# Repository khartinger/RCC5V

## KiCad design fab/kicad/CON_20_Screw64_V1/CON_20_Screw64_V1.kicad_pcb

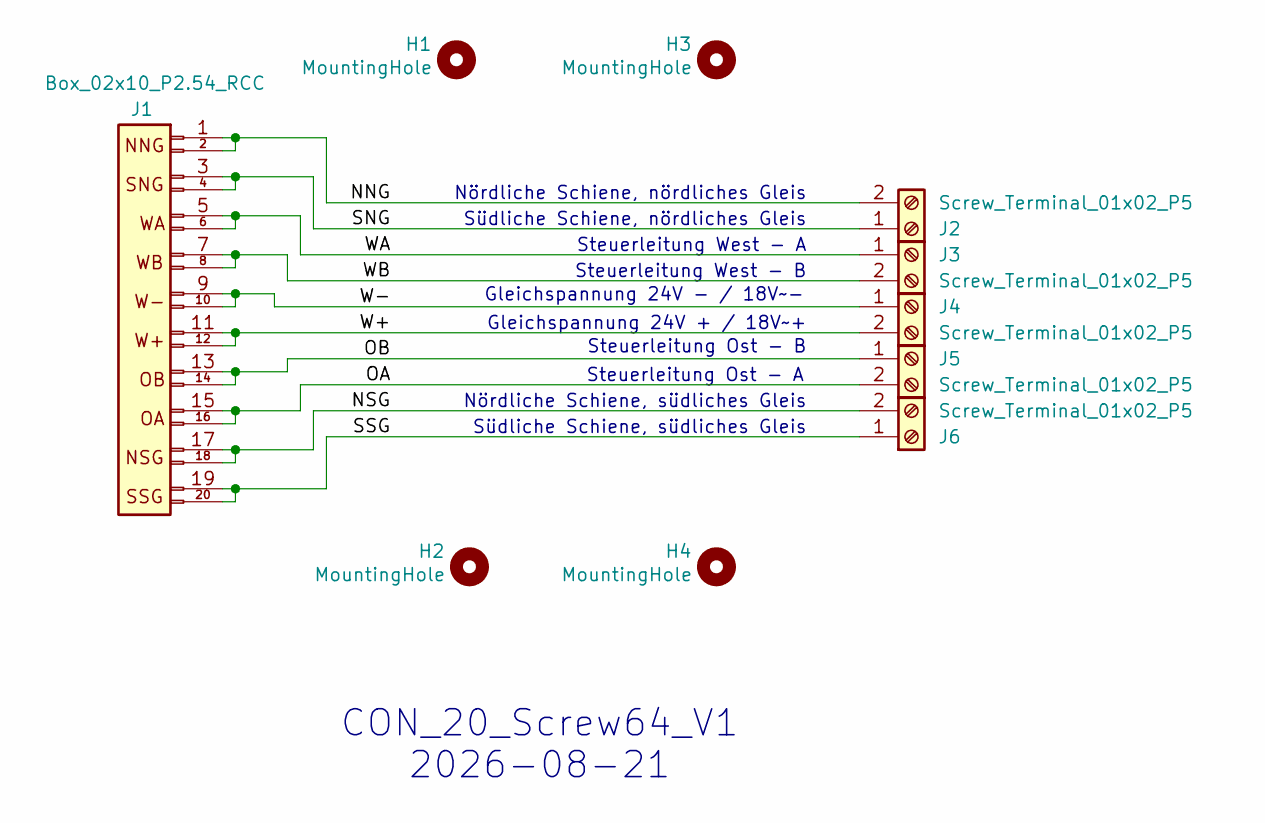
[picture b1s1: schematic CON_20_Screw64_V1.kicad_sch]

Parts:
H1, H2, H3, H4: MountingHole; MountingHole_2.7mm_M2.5_DIN965_Pad_TopBottom
J1: Box_02x10_P2.54_RCC; Box_02x10_P2.54mm_Vertical_kh
J2, J3, J4, J5, J6: Screw_Terminal_01x02_P5

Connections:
/NNG: J1.1, J1.2, J2.2
/NSG: J1.17, J1.18, J6.2
/OA: J1.15, J1.16, J5.2
/OB: J1.13, J1.14, J5.1
/SNG: J1.3, J1.4, J2.1
/SSG: J1.19, J1.20, J6.1
/W+: J1.11, J1.12, J4.2
/W-: J1.9, J1.10, J4.1
/WA: J1.5, J1.6, J3.1
/WB: J1.7, J1.8, J3.2

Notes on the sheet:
CON_20_Screw64_V1 2026-08-21
Südliche Schiene, südliches Gleis
Südliche Schiene, nördliches Gleis
Gleichspannung 24V - / 18V~-
Nördliche Schiene, nördliches Gleis
Steuerleitung West - A
Steuerleitung Ost - B
Steuerleitung West - B
Gleichspannung 24V + / 18V~+
Nördliche Schiene, südliches Gleis
Steuerleitung Ost - A

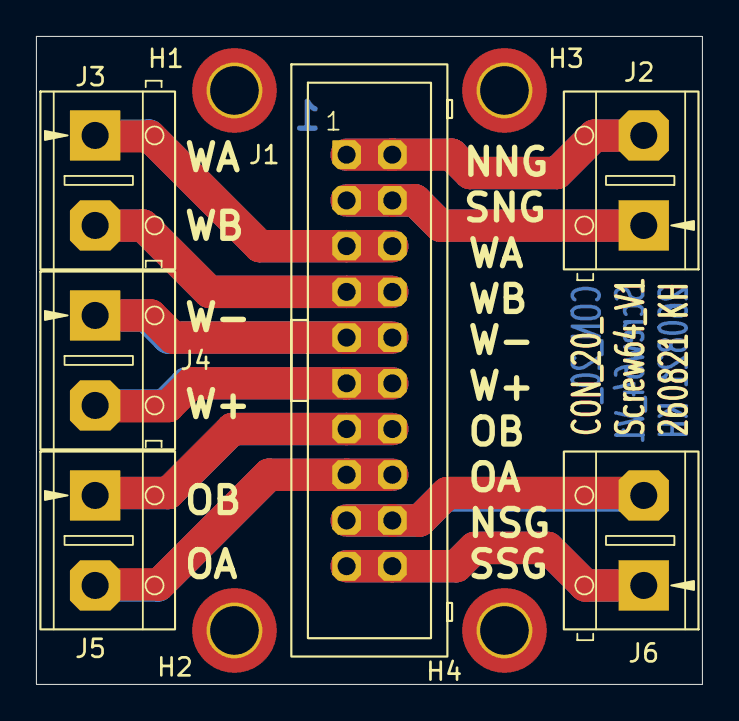
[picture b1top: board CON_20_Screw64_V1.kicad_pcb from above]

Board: 2 copper layers, 37.0 x 36.0 mm, 10 parts (0 on the bottom side), 10 nets.

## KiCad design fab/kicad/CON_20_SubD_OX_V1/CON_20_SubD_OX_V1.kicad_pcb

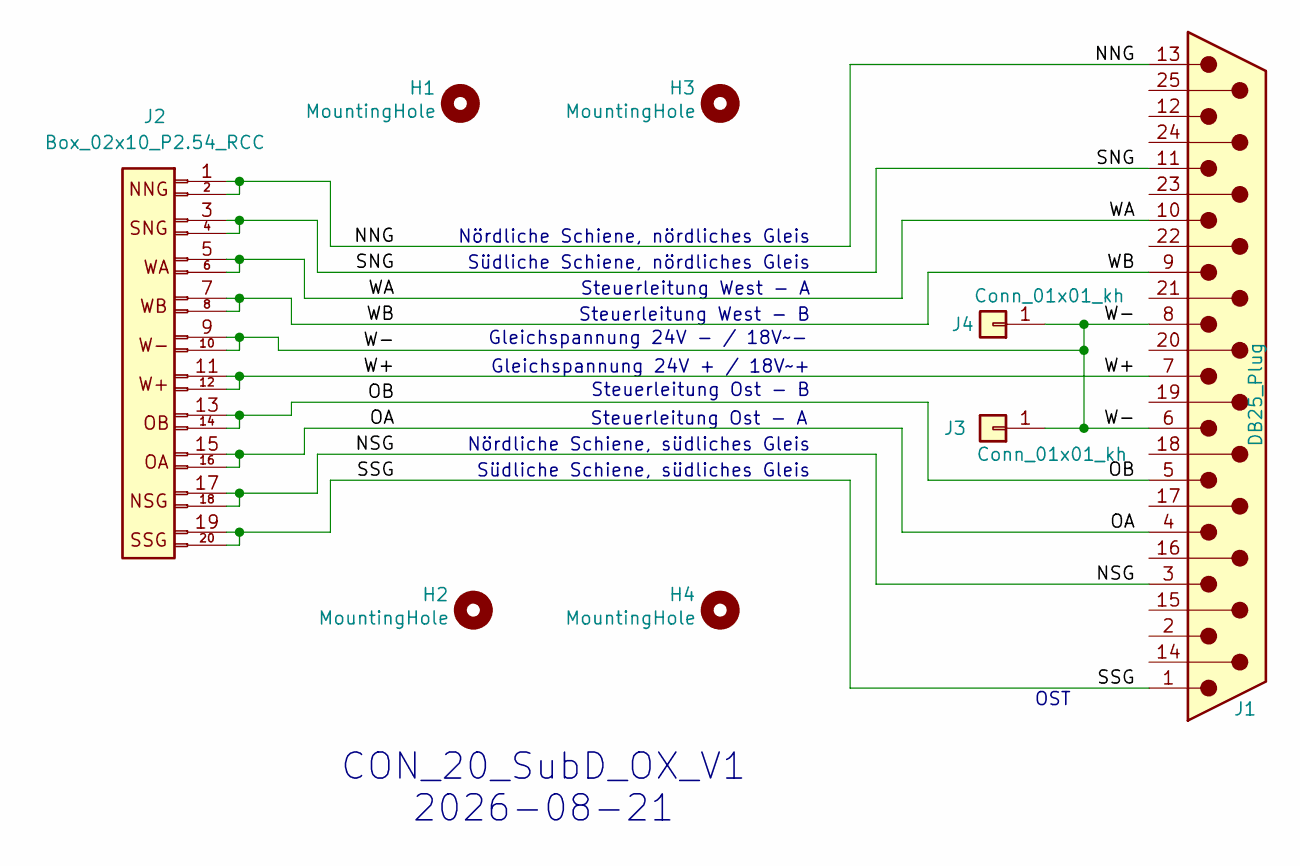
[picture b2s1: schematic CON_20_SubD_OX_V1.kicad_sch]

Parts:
H1, H2, H3, H4: MountingHole; MountingHole_2.7mm_M2.5_DIN965_Pad_TopBottom
J1: DB25_Plug; DSUB-25_Male_Horizontal_P2.77x2.84mm_EdgePinOffset7.70mm_Ho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
J2: Box_02x10_P2.54_RCC; Box_02x10_P2.54mm_Vertical_kh
J3, J4: Conn_01x01_kh; Pin_D0.9mm_W1.4mm

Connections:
/NNG: J1.13, J2.1, J2.2
/NSG: J1.3, J2.17, J2.18
/OA: J1.4, J2.15, J2.16
/OB: J1.5, J2.13, J2.14
/SNG: J1.11, J2.3, J2.4
/SSG: J1.1, J2.19, J2.20
/W+: J1.7, J2.11, J2.12
/W-: J1.6, J1.8, J2.9, J2.10, J3.1 (Pin_1_1), J4.1 (Pin_1_1)
/WA: J1.10, J2.5, J2.6
/WB: J1.9, J2.7, J2.8

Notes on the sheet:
CON_20_SubD_OX_V1 2026-08-21
Südliche Schiene, südliches Gleis
Südliche Schiene, nördliches Gleis
Gleichspannung 24V - / 18V~-
Nördliche Schiene, nördliches Gleis
Steuerleitung West - A
Steuerleitung Ost - B
Steuerleitung West - B
OST
Gleichspannung 24V + / 18V~+
Nördliche Schiene, südliches Gleis
Steuerleitung Ost - A

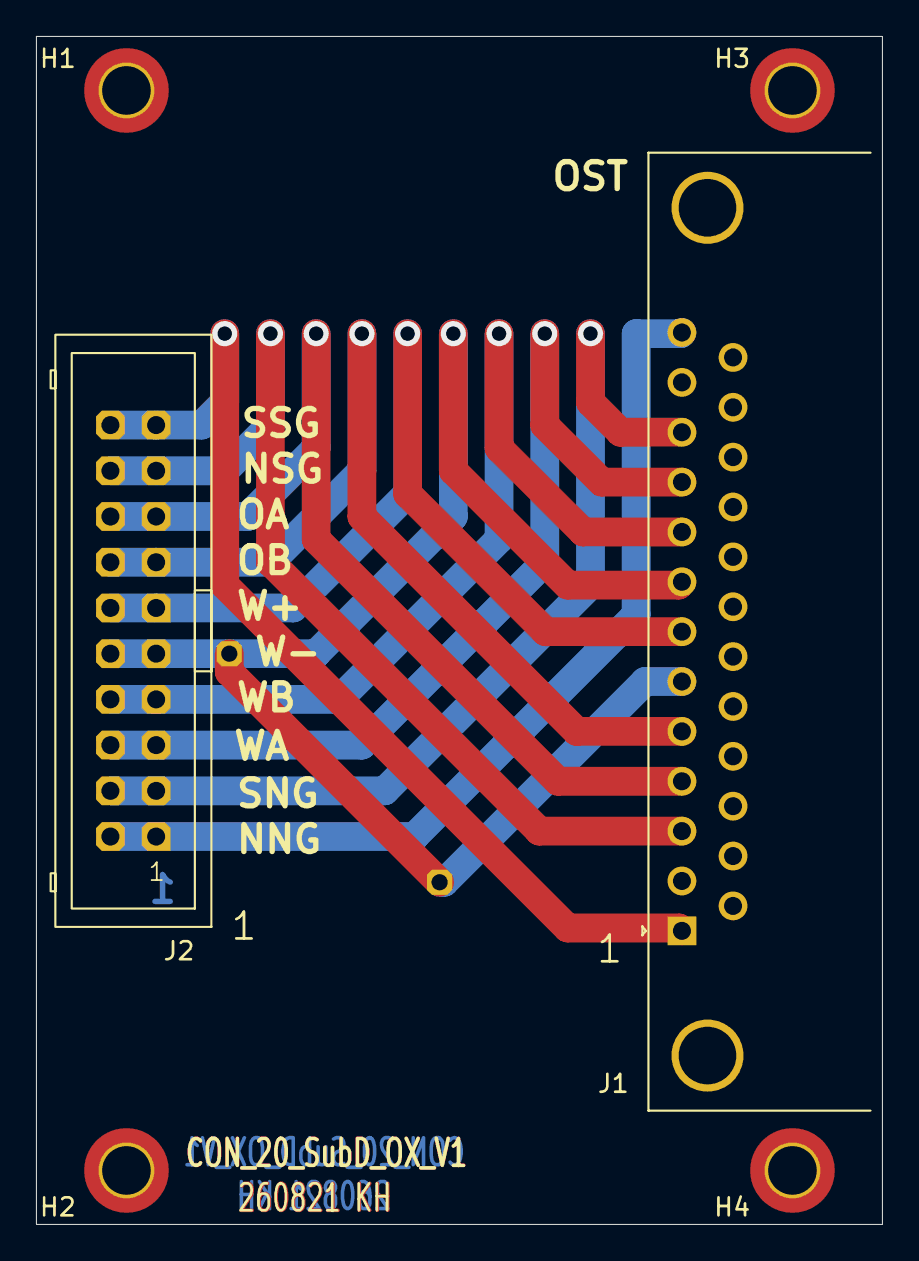
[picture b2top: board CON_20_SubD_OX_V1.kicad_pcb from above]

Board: 2 copper layers, 47.0 x 66.0 mm, 8 parts (0 on the bottom side), 10 nets.

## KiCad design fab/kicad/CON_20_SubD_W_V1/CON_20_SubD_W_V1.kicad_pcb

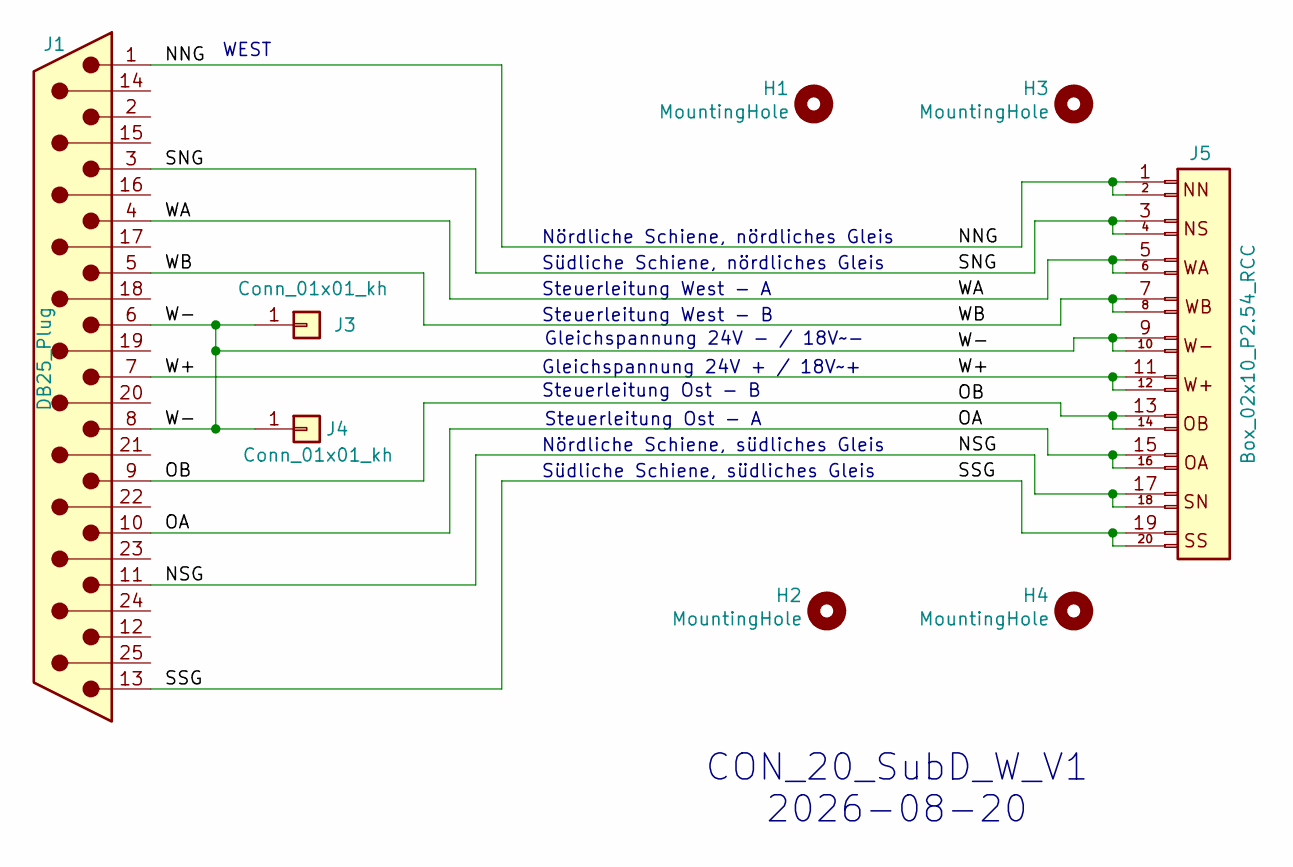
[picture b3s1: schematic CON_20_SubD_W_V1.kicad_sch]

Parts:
H1, H2, H3, H4: MountingHole; MountingHole_2.7mm_M2.5_DIN965_Pad_TopBottom
J1: DB25_Plug; DSUB-25_Male_Horizontal_P2.77x2.84mm_EdgePinOffset7.70mm_Ho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
J3, J4: Conn_01x01_kh; Pin_D0.9mm_W1.4mm
J5: Box_02x10_P2.54_RCC; Box_02x10_P2.54mm_Vertical_kh

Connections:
/NNG: J1.1, J5.1, J5.2
/NSG: J1.11, J5.17, J5.18
/OA: J1.10, J5.15, J5.16
/OB: J1.9, J5.13, J5.14
/SNG: J1.3, J5.3, J5.4
/SSG: J1.13, J5.19, J5.20
/W+: J1.7, J5.11, J5.12
/W-: J1.6, J1.8, J3.1 (Pin_1_1), J4.1 (Pin_1_1), J5.9, J5.10
/WA: J1.4, J5.5, J5.6
/WB: J1.5, J5.7, J5.8

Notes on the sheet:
CON_20_SubD_W_V1 2026-08-20
Südliche Schiene, südliches Gleis
Südliche Schiene, nördliches Gleis
Gleichspannung 24V - / 18V~-
Nördliche Schiene, nördliches Gleis
Steuerleitung West - A
Steuerleitung Ost - B
Steuerleitung West - B
WEST
Gleichspannung 24V + / 18V~+
Nördliche Schiene, südliches Gleis
Steuerleitung Ost - A

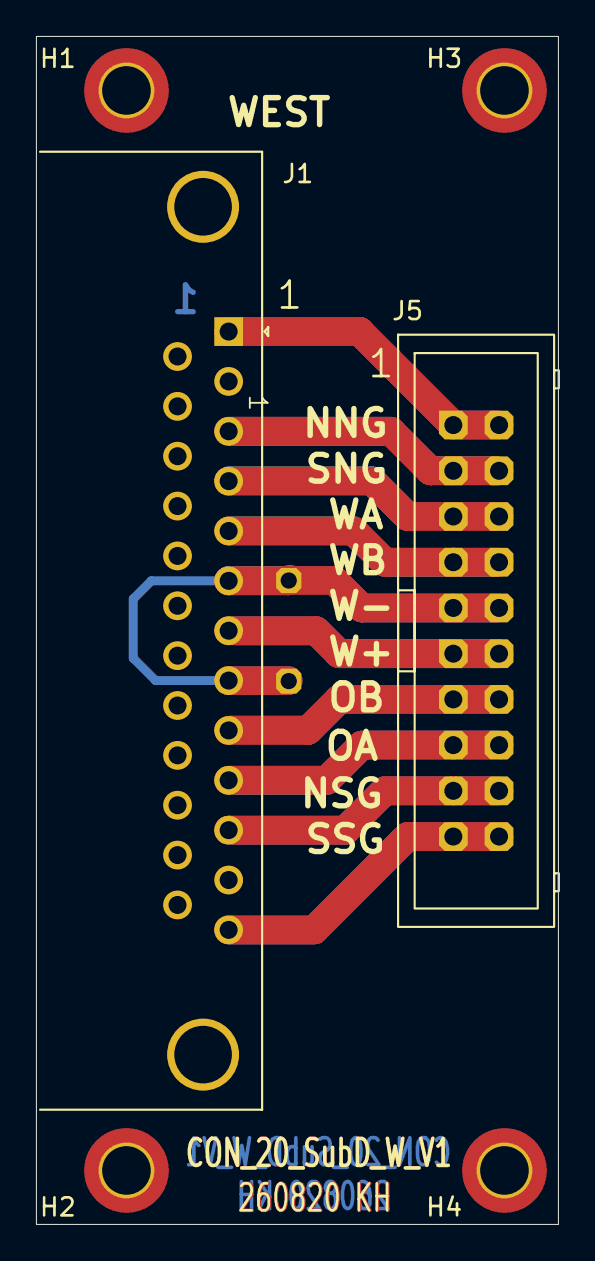
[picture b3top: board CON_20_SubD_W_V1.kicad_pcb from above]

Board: 2 copper layers, 29.0 x 66.0 mm, 8 parts (0 on the bottom side), 10 nets.

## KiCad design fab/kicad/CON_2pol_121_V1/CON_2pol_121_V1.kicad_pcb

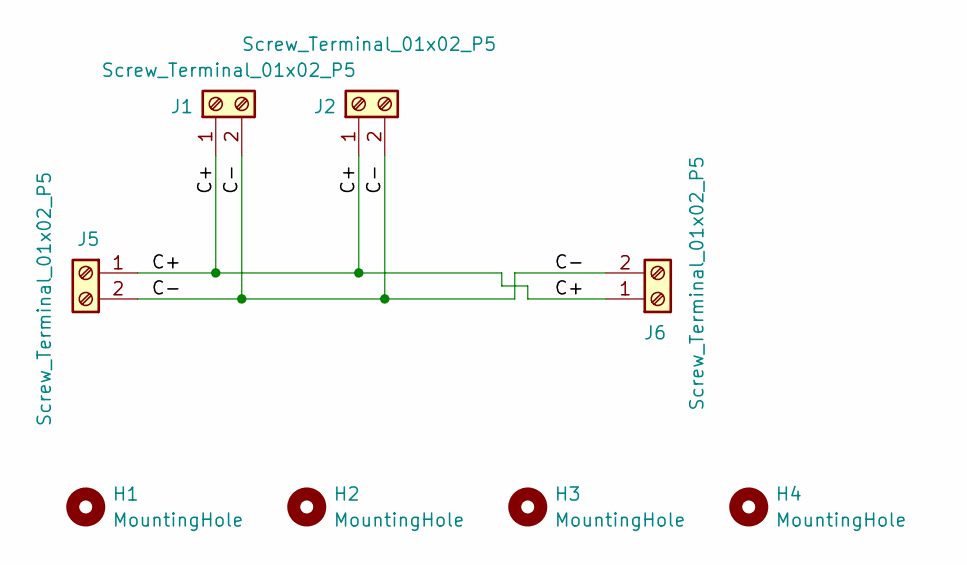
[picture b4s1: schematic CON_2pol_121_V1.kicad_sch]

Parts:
H1, H2, H3, H4: MountingHole; MountingHole_2.2mm_M2_Pad_TopBottom_kh
J1, J2, J5, J6: Screw_Terminal_01x02_P5

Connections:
/C+: J1.1, J2.1, J5.1, J6.1
/C-: J1.2, J2.2, J5.2, J6.2

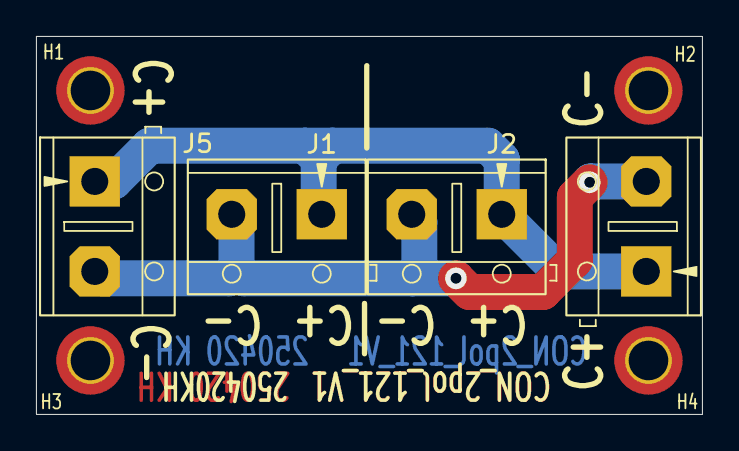
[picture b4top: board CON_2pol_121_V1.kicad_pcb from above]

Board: 2 copper layers, 37.0 x 21.0 mm, 8 parts (0 on the bottom side), 2 nets.

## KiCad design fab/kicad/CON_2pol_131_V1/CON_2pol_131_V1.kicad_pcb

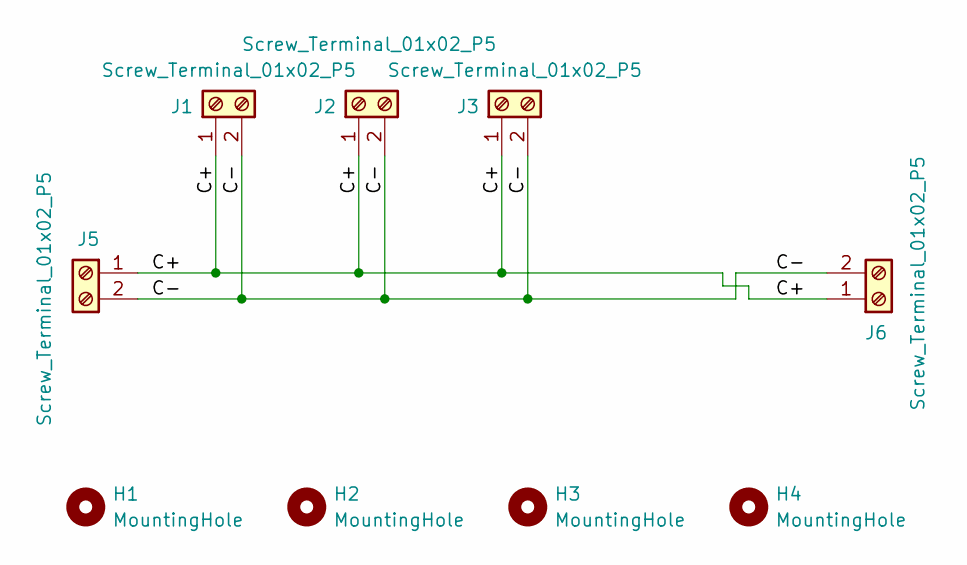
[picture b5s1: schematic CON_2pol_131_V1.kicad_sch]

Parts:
H1, H2, H3, H4: MountingHole; MountingHole_2.2mm_M2_Pad_TopBottom_kh
J1, J2, J3, J5, J6: Screw_Terminal_01x02_P5

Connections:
/C+: J1.1, J2.1, J3.1, J5.1, J6.1
/C-: J1.2, J2.2, J3.2, J5.2, J6.2

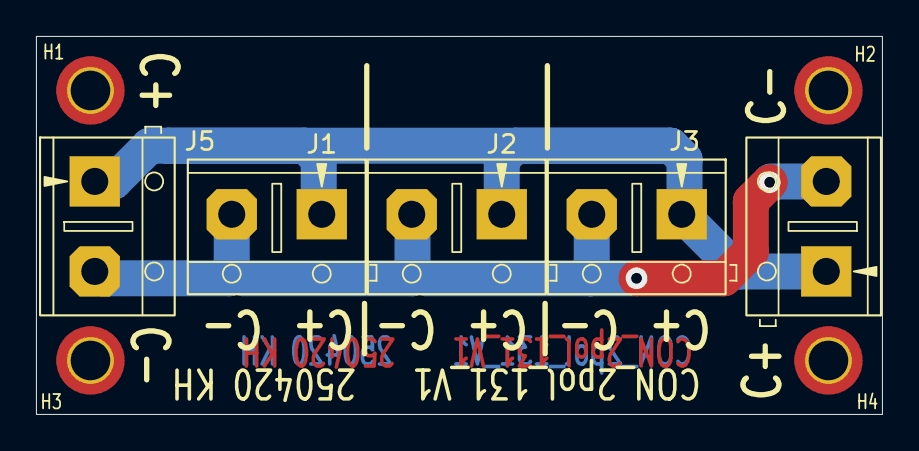
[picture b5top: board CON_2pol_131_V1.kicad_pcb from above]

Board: 2 copper layers, 47.0 x 21.0 mm, 9 parts (0 on the bottom side), 2 nets.

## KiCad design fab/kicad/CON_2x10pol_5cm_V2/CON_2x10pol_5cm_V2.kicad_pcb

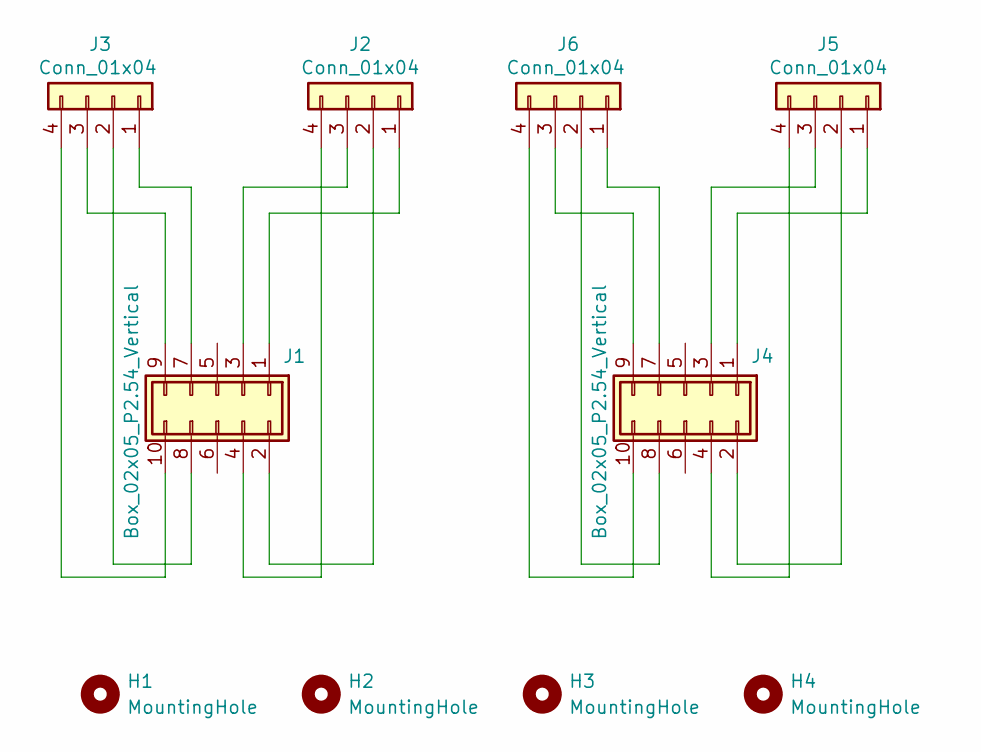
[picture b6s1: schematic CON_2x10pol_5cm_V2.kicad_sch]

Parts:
H1, H2, H3, H4: MountingHole; MountingHole_2.2mm_M2_Pad_TopBottom_kh
J1, J4: Box_02x05_P2.54_Vertical; Box_02x05_P2.54mm_Vertical_kh
J2, J3, J5, J6: Conn_01x04; PinSocket_1x04_P2.54mm_Vertical_kh

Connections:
unnamed: J1.1, J2.1
unnamed: J1.2, J2.2
unnamed: J1.3, J2.3
unnamed: J1.4, J2.4
unnamed: J1.7, J3.1
unnamed: J1.8, J3.2
unnamed: J1.9, J3.3
unnamed: J1.10, J3.4
unnamed: J4.1, J5.1
unnamed: J4.2, J5.2
unnamed: J4.3, J5.3
unnamed: J4.4, J5.4
unnamed: J4.7, J6.1
unnamed: J4.8, J6.2
unnamed: J4.9, J6.3
unnamed: J4.10, J6.4

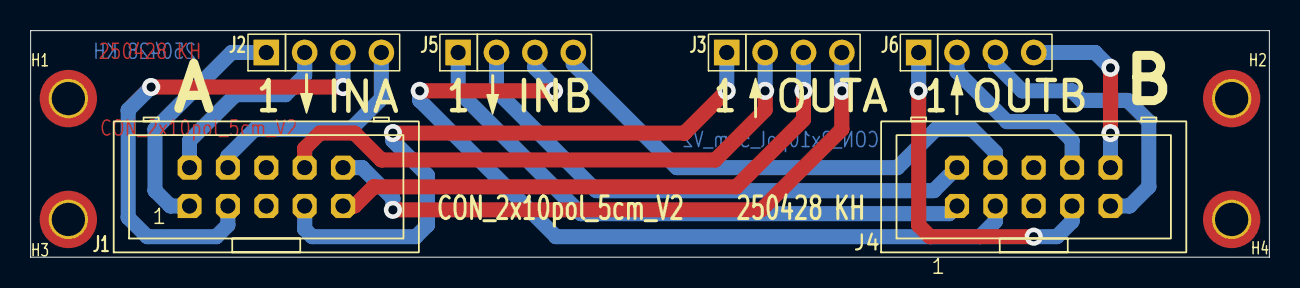
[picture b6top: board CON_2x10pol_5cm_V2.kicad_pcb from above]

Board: 2 copper layers, 82.0 x 15.0 mm, 10 parts (0 on the bottom side), 16 nets.
